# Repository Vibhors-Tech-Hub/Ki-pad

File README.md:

# Ki-pad

Alright, so while working in KiCad, I need to use a lot of shortcuts. And not only are there many, but they're also a bit easy to mess up. So, while Hack Club recommends Macropads specifically to beginners, I decided to give it a go, without making things much complex, so I could have a easier, and more power workflow! And that also explains it's *unique* name!

# Features

So, with the number of shortcuts in KiCad that I use almost daily, I decided that a Macropad with **12 MX2A-H1NA keys** would be great. And I also added **two PEC11R-4220F-S0024 rotary encoders**; one for zooming in and zooming out (not only for KiCad), and one for scrolling (through massive datasheets).

So, I had two options for the switches then, either route each of them separately to my controller, or use a **matrix-based configuration** with rows and columns. I chose the later as it not only uses way less GPIOs, but most open-source projects and firmwares use it.

So, for the controller, I realised most projects on one way or the other use the RP2040. So, I too went with it. To keep things simple I decided to use a dev-board instead of using the raw QFN-56. Requiring **12 GPIOs**, the widely used Seed Studio RP2040 XIAO fell short by just one GPIO. So, I went with the **Waveshare RP2040 Zero** board.

I said that I didn't want to make this much complex, but what's a Macropad without lights? So, I also used **12 SK6812MINI-E RGB LEDs**, all daisy-chained underneath the switches. The SK6812MINI-E operate on 5V, and the min voltage to control them, according to the datasheet is 5 * 0.7 = 3.5V. As the RP2040's GPIO pins are only 3.3V tolerant, I had to go with a **74AHCT1G125 logic-level shifter**

As I said, to keep things simple, I didn't add a OLED, though it could be used for *something*?

# Enclosure

For this revision, I didn't design an enclosure. I didn't think it was absolutely required, as I was just making it to make my daily workflow easier, and while I've designed a LOT of PCBs, I'm a newbie to 3D CAD designing. But I could aways design one with MDF if I need it when I get the PCB in hand; whihcb is exactly why I added 4 M2.5 mounting holes.

# Firmware

Now, to actually map keys and rotary encoders to their functions, I had two options. Either to write my own firmware, or use Vial. Now, I could write my own firmware, but considering I just wanted it to help me with KiCad, and I wanted to keep it highly customizable, I decided to go with Vial. Vial uses an interactive GUI to assign shortcuts to switches instantly, and in the end generates a .uf2 file I can flash onto my RP2040. But it has a catch; I must physically plug-in my device to program it. Hence, I don't have any firmware inside it currently. But as soon as I get the PCB, I'll commit a .uf2 file in a firmware directory.

# Schematic

# PCB

# 3D view

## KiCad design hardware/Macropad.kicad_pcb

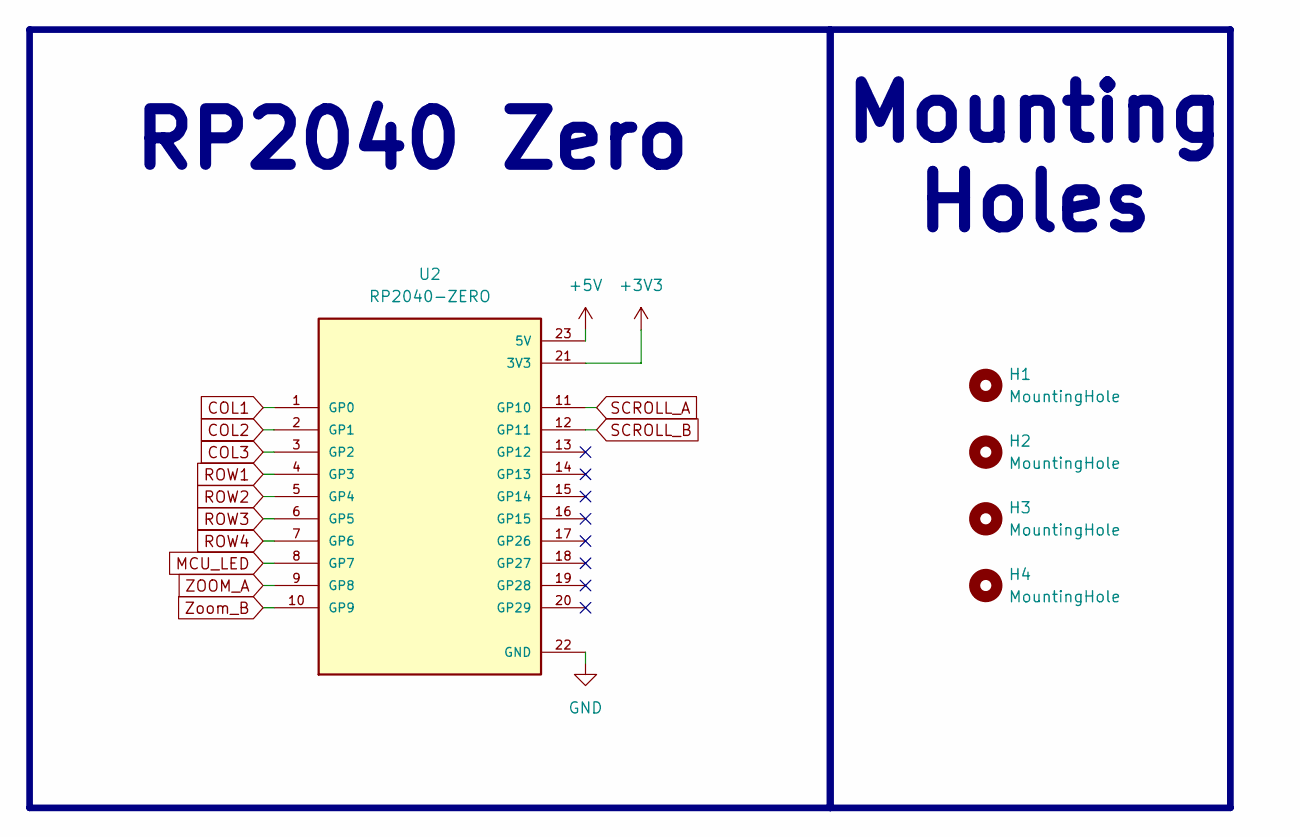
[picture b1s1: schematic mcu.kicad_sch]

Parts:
H1, H2, H3, H4: MountingHole; MountingHole_2.7mm_M2.5
U2: RP2040-ZERO; PARTREV NA

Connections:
+3V3: U2.21 (3V3); also elsewhere on the board
+5V: U2.23 (5V); also elsewhere on the board
COL1: U2.1 (GP0); also elsewhere on the board
COL2: U2.2 (GP1); also elsewhere on the board
COL3: U2.3 (GP2); also elsewhere on the board
GND: U2.22 (GND); also elsewhere on the board
MCU_LED: U2.8 (GP7); also elsewhere on the board
ROW1: U2.4 (GP3); also elsewhere on the board
ROW2: U2.5 (GP4); also elsewhere on the board
ROW3: U2.6 (GP5); also elsewhere on the board
ROW4: U2.7 (GP6); also elsewhere on the board
SCROLL_A: U2.11 (GP10); also elsewhere on the board
SCROLL_B: U2.12 (GP11); also elsewhere on the board
ZOOM_A: U2.9 (GP8); also elsewhere on the board
Zoom_B: U2.10 (GP9); also elsewhere on the board

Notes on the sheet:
Mounting Holes
RP2040 Zero

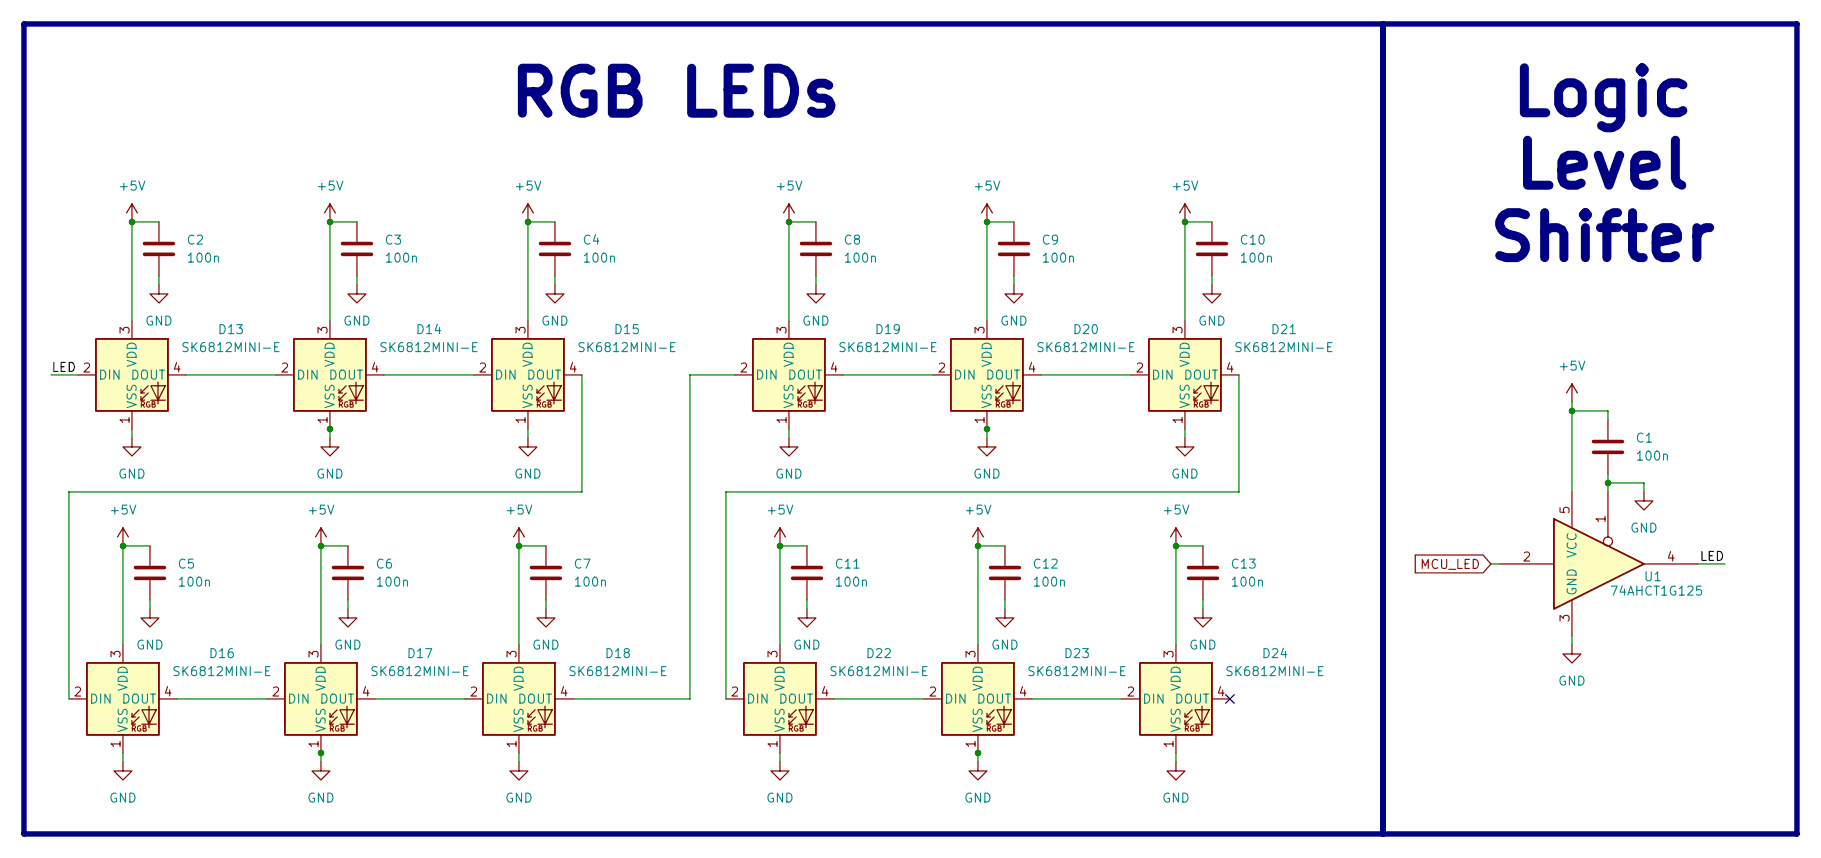
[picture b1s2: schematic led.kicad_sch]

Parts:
C1, C2, C3, C4, C5, C6, C7, C8, C9, C10, C11, C12, C13: 100n; C_0805_2012Metric_Pad1.18x1.45mm_HandSolder
D13, D14, D15, D16, D17, D18, D19, D20, D21, D22, D23, D24: SK6812MINI-E; LED_SK6812MINI-E_3.2x2.8mm_P1.5mm_ReverseMount
U1: 74AHCT1G125; SOT-23-5_HandSoldering

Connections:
+5V: C1.1, C2.1, C3.1, C4.1, C5.1, C6.1, C7.1, C8.1, C9.1, C10.1, C11.1, C12.1, C13.1, D13.3 (VDD), D14.3 (VDD), D15.3 (VDD), D16.3 (VDD), D17.3 (VDD), D18.3 (VDD), D19.3 (VDD), D20.3 (VDD), D21.3 (VDD), D22.3 (VDD), D23.3 (VDD), D24.3 (VDD), U1.5 (VCC); also elsewhere on the board
/LED/LED: D13.2 (DIN), U1.4
GND: C1.2, C2.2, C3.2, C4.2, C5.2, C6.2, C7.2, C8.2, C9.2, C10.2, C11.2, C12.2, C13.2, D13.1 (VSS), D14.1 (VSS), D15.1 (VSS), D16.1 (VSS), D17.1 (VSS), D18.1 (VSS), D19.1 (VSS), D20.1 (VSS), D21.1 (VSS), D22.1 (VSS), D23.1 (VSS), D24.1 (VSS), U1.1, U1.3 (GND); also elsewhere on the board
MCU_LED: U1.2; also elsewhere on the board
unnamed: D13.4 (DOUT), D14.2 (DIN)
unnamed: D14.4 (DOUT), D15.2 (DIN)
unnamed: D15.4 (DOUT), D16.2 (DIN)
unnamed: D16.4 (DOUT), D17.2 (DIN)
unnamed: D17.4 (DOUT), D18.2 (DIN)
unnamed: D18.4 (DOUT), D19.2 (DIN)
unnamed: D19.4 (DOUT), D20.2 (DIN)
unnamed: D20.4 (DOUT), D21.2 (DIN)
unnamed: D21.4 (DOUT), D22.2 (DIN)
unnamed: D22.4 (DOUT), D23.2 (DIN)
unnamed: D23.4 (DOUT), D24.2 (DIN)

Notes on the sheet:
RGB LEDs
Logic Level Shifter

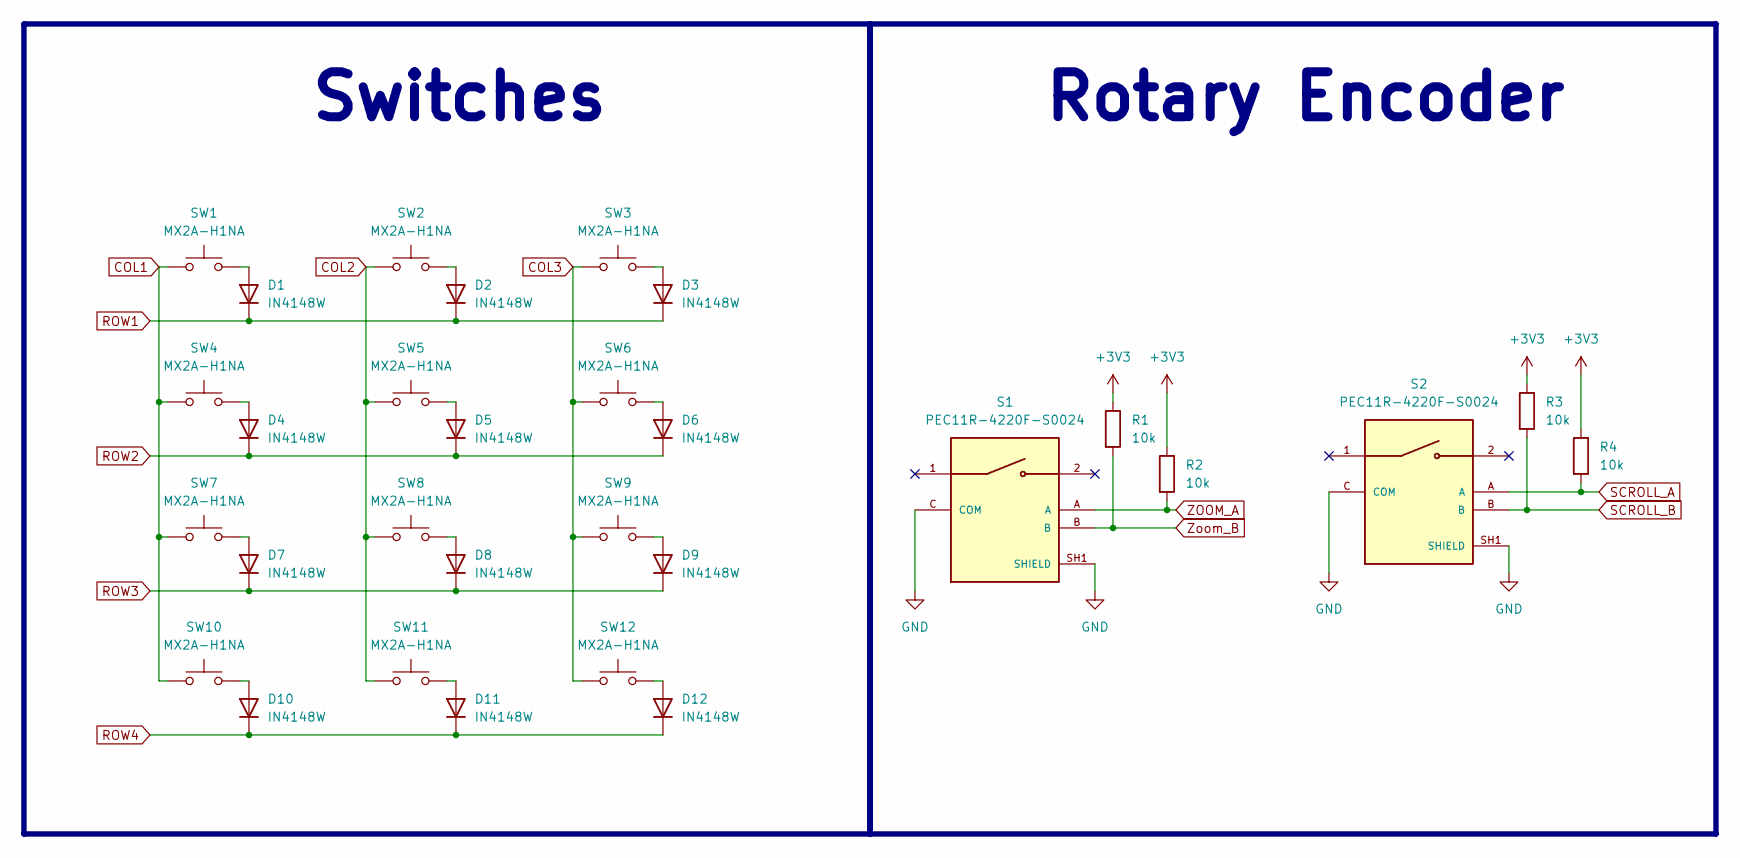
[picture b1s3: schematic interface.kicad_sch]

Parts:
D1, D2, D3, D4, D5, D6, D7, D8, D9, D10, D11, D12: IN4148W; D_SOD-123F
R1, R2, R3, R4: 10k; R_0805_2012Metric_Pad1.20x1.40mm_HandSolder
S1, S2: PEC11R-4220F-S0024; PARTREV 11/23
SW1, SW2, SW3, SW4, SW5, SW6, SW7, SW8, SW9, SW10, SW11, SW12: MX2A-H1NA; MX1A-11NN

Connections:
+3V3: R1.1, R2.1, R3.1, R4.1; also elsewhere on the board
COL1: SW1.1, SW4.1, SW7.1, SW10.1; also elsewhere on the board
COL2: SW2.1, SW5.1, SW8.1, SW11.1; also elsewhere on the board
COL3: SW3.1, SW6.1, SW9.1, SW12.1; also elsewhere on the board
GND: S1.C (COM), S1.SH1 (SHIELD), S1.SH2 (SHIELD), S2.C (COM), S2.SH1 (SHIELD), S2.SH2 (SHIELD); also elsewhere on the board
unnamed: D1.2 (A), SW1.2
unnamed: D2.2 (A), SW2.2
unnamed: D3.2 (A), SW3.2
unnamed: D4.2 (A), SW4.2
unnamed: D5.2 (A), SW5.2
unnamed: D6.2 (A), SW6.2
unnamed: D7.2 (A), SW7.2
unnamed: D8.2 (A), SW8.2
unnamed: D9.2 (A), SW9.2
unnamed: D10.2 (A), SW10.2
unnamed: D11.2 (A), SW11.2
unnamed: D12.2 (A), SW12.2
ROW1: D1.1 (K), D2.1 (K), D3.1 (K); also elsewhere on the board
ROW2: D4.1 (K), D5.1 (K), D6.1 (K); also elsewhere on the board
ROW3: D7.1 (K), D8.1 (K), D9.1 (K); also elsewhere on the board
ROW4: D10.1 (K), D11.1 (K), D12.1 (K); also elsewhere on the board
SCROLL_A: R4.2, S2.A; also elsewhere on the board
SCROLL_B: R3.2, S2.B; also elsewhere on the board
ZOOM_A: R2.2, S1.A; also elsewhere on the board
Zoom_B: R1.2, S1.B; also elsewhere on the board

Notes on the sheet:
Rotary Encoder
Switches

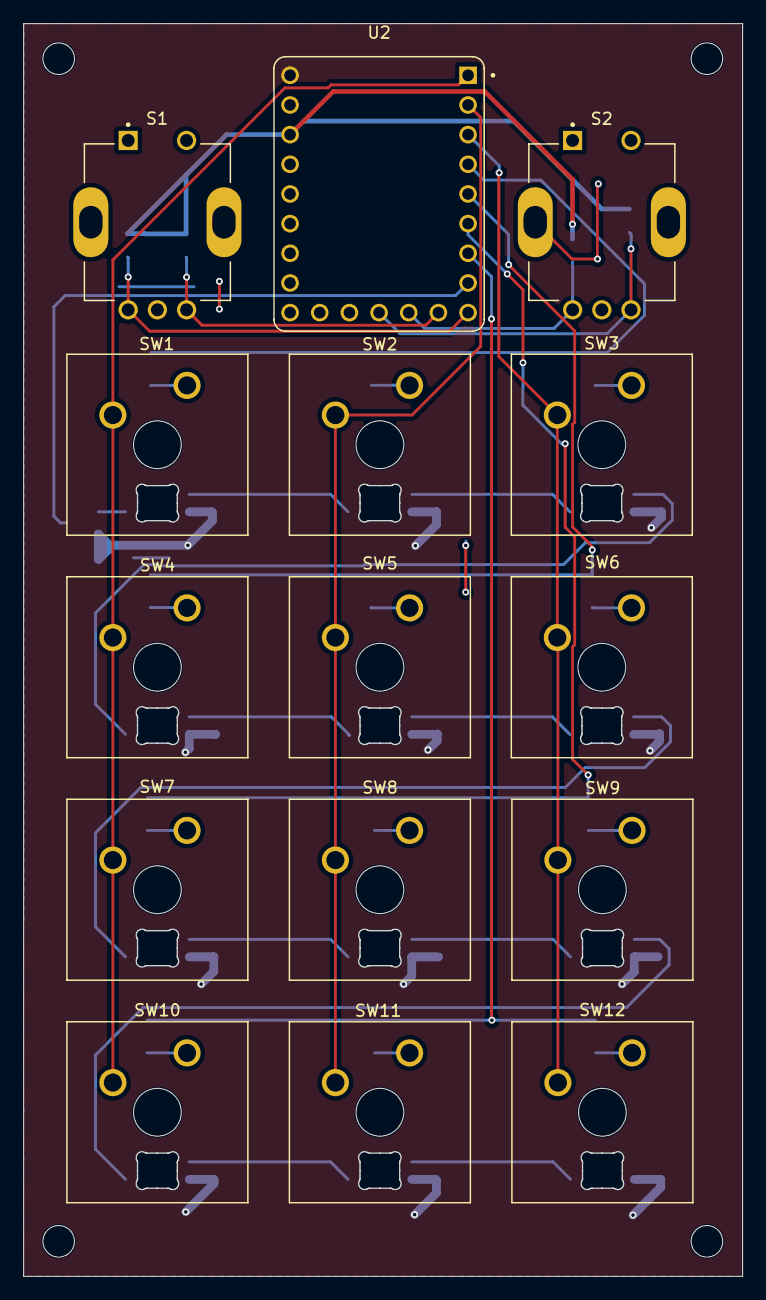
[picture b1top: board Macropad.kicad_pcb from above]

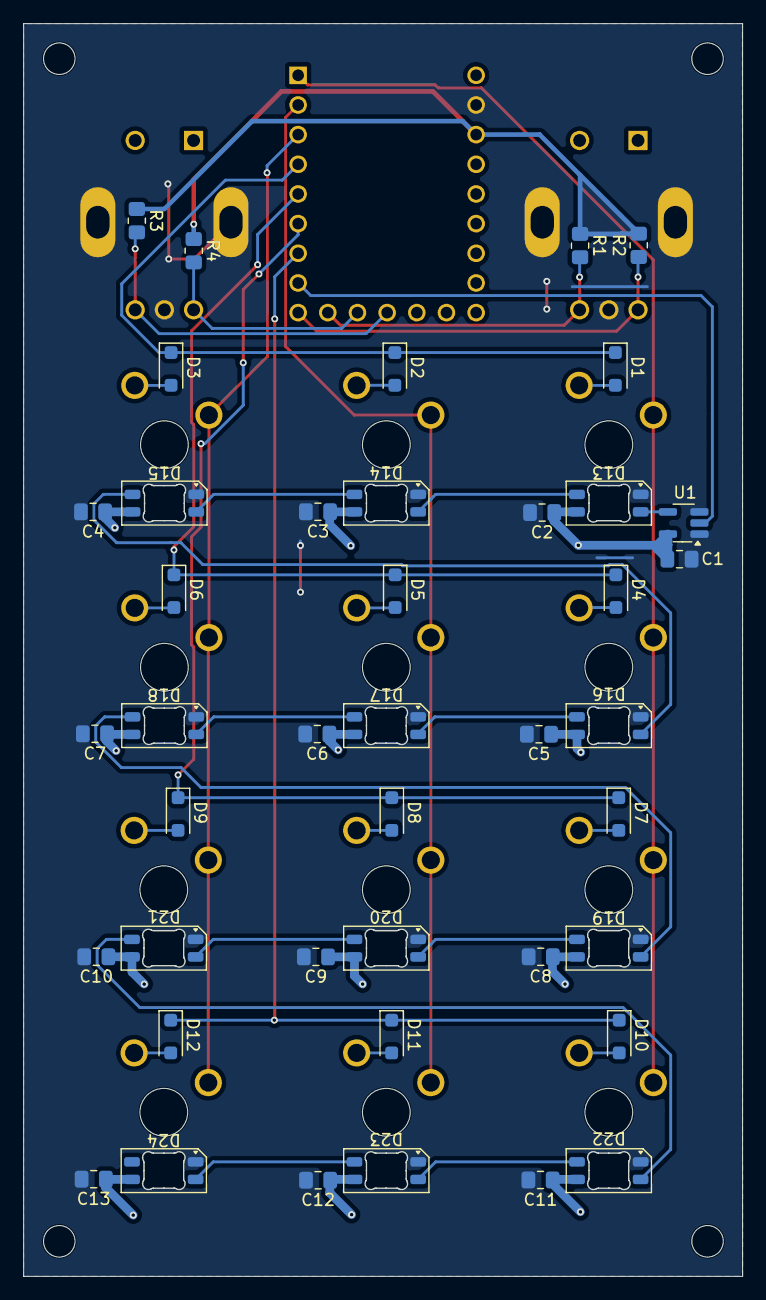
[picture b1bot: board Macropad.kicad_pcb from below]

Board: 2 copper layers, 61.6 x 107.2 mm, 61 parts (42 on the bottom side), 39 nets.

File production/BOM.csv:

"Id";"Designator";"Footprint";"Quantity";"Designation";"Supplier and ref";
1;"C1, C2, C3, C4, C5, C6, C7, C8, C9, C10, C11, C12, C13";"C_0805_2012Metric_Pad1.18x1.45mm_HandSolder";13;"100n";;;
2;"D1, D2, D3, D4, D5, D6, D7, D8, D9, D10, D11, D12";"D_SOD-123F";12;"IN4148W";;;
3;"D13, D14, D15, D16, D17, D18, D19, D20, D21, D22, D23, D24";"LED_SK6812MINI-E_3.2x2.8mm_P1.5mm_ReverseMount";12;"SK6812MINI-E";;;
4;"R1, R2, R3, R4";"R_0805_2012Metric_Pad1.20x1.40mm_HandSolder";4;"10k";;;
5;"S1, S2";"PEC11R-4220F-S0024";2;"PEC11R-4220F-S0024";;;
6;"SW1, SW2, SW3, SW4, SW5, SW6, SW7, SW8, SW9, SW10, SW11, SW12";"MX1A-11NN";12;"MX2A-H1NA";;;
7;"U1";"SOT-23-5_HandSoldering";1;"74AHCT1G125";;;
8;"U2";"RP2040-ZERO";1;"RP2040-ZERO";;;
